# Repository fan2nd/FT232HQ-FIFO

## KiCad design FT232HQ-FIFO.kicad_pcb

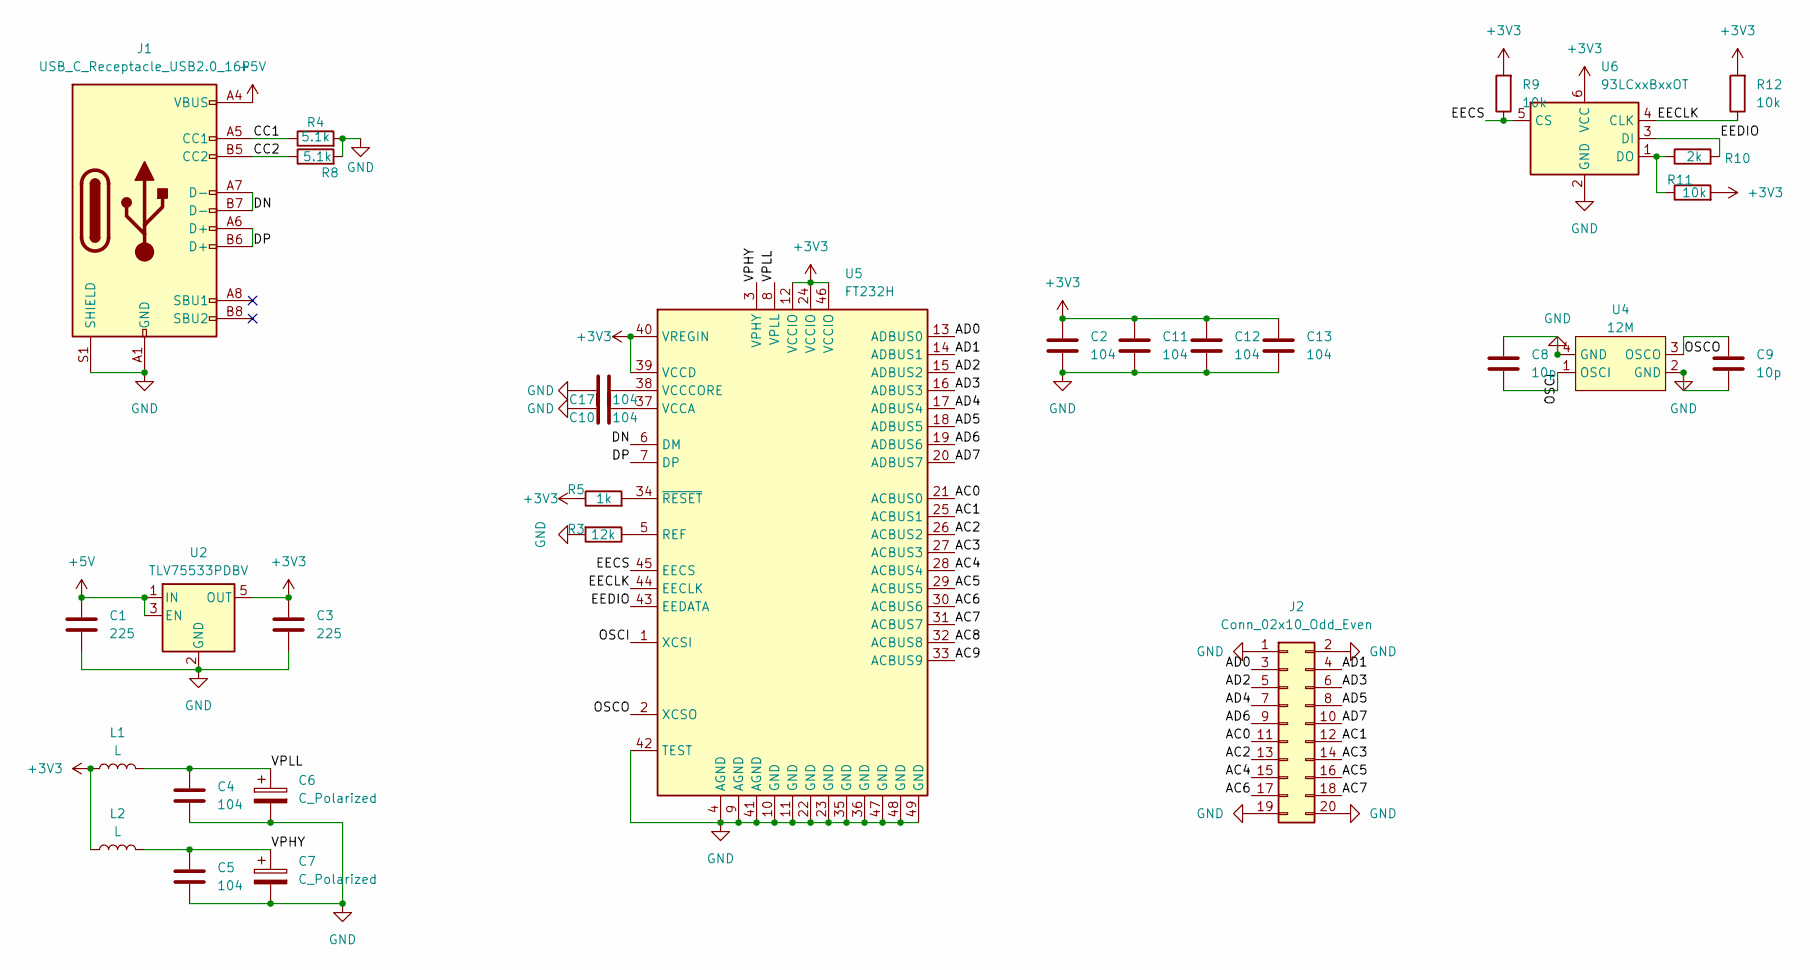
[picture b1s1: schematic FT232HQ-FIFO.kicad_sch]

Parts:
C1, C3: 225; C_0402_1005Metric
C2, C4, C5, C10, C11, C12, C13, C17: 104; C_0402_1005Metric
C6, C7: C_Polarized; C_0603_1608Metric
C8, C9: 10p; C_0402_1005Metric
J1: USB_C_Receptacle_USB2.0_16P; USB_C_Receptacle_TYPE-C-12P
J2: Conn_02x10_Odd_Even; PinHeader_2x10_P2.54mm_Vertical
L1, L2: L; L_0603_1608Metric
R3: 12k; R_0402_1005Metric
R4, R8: 5.1k; R_0402_1005Metric
R5: 1k; R_0402_1005Metric
R9, R11, R12: 10k; R_0402_1005Metric
R10: 2k; R_0402_1005Metric
U2: TLV75533PDBV; SOT-23-5
U4: 12M; Oscillator_SMD_13_3.2x2.5mm
U5: FT232H; QFN-48-1EP_8x8mm_P0.5mm_EP6.2x6.2mm
U6: 93LCxxBxxOT; SOT-23-6

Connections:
+3V3: C2.1, C3.1, C11.1, C12.1, C13.1, L1.1, L2.1, R5.1, R9.2, R11.2, R12.2, U2.5 (OUT), U5.12 (VCCIO), U5.24 (VCCIO), U5.39 (VCCD), U5.40 (VREGIN), U5.46 (VCCIO), U6.6 (VCC)
+5V: C1.1, J1.A4 (VBUS), J1.A9 (VBUS), J1.B4 (VBUS), J1.B9 (VBUS), U2.1 (IN), U2.3 (EN)
/AC0: J2.11, U5.21 (ACBUS0)
/AC1: J2.12, U5.25 (ACBUS1)
/AC2: J2.13, U5.26 (ACBUS2)
/AC3: J2.14, U5.27 (ACBUS3)
/AC4: J2.15, U5.28 (ACBUS4)
/AC5: J2.16, U5.29 (ACBUS5)
/AC6: J2.17, U5.30 (ACBUS6)
/AC7: J2.18, U5.31 (ACBUS7)
/AC8: U5.32 (ACBUS8)
/AC9: U5.33 (ACBUS9)
/AD0: J2.3, U5.13 (ADBUS0)
/AD1: J2.4, U5.14 (ADBUS1)
/AD2: J2.5, U5.15 (ADBUS2)
/AD3: J2.6, U5.16 (ADBUS3)
/AD4: J2.7, U5.17 (ADBUS4)
/AD5: J2.8, U5.18 (ADBUS5)
/AD6: J2.9, U5.19 (ADBUS6)
/AD7: J2.10, U5.20 (ADBUS7)
/CC1: J1.A5 (CC1), R4.1
/CC2: J1.B5 (CC2), R8.1
/DN: J1.A7 (D-), J1.B7 (D-), U5.6 (DM)
/DP: J1.A6 (D+), J1.B6 (D+), U5.7 (DP)
/EECLK: R12.1, U5.44 (EECLK), U6.4 (CLK)
/EECS: R9.1, U5.45 (EECS), U6.5 (CS)
/EEDIO: R10.2, U5.43 (EEDATA), U6.3 (DI)
/OSCI: C8.2, U4.1 (OSCI), U5.1 (XCSI)
/OSCO: C9.2, U4.3 (OSCO), U5.2 (XCSO)
/VPHY: C5.1, C7.1, L2.2, U5.3 (VPHY)
/VPLL: C4.1, C6.1, L1.2, U5.8 (VPLL)
GND: C1.2, C2.2, C3.2, C4.2, C5.2, C6.2, C7.2, C8.1, C9.1, C10.1, C11.2, C12.2, C13.2, C17.1, J1.A1 (GND), J1.A12 (GND), J1.B1 (GND), J1.B12 (GND), J1.S1 (SHIELD), J2.1, J2.2, J2.19, J2.20, R3.2, R4.2, R8.2, U2.2 (GND), U4.2 (GND), U4.4 (GND), U5.4 (AGND), U5.9 (AGND), U5.10 (GND), U5.11 (GND), U5.22 (GND), U5.23 (GND), U5.35 (GND), U5.36 (GND), U5.41 (AGND), U5.42 (TEST), U5.47 (GND), U5.48 (GND), U5.49 (GND), U6.2 (GND)
unnamed: R3.1, U5.5 (REF)
unnamed: C10.2, U5.37 (VCCA)
unnamed: C17.2, U5.38 (VCCCORE)
unnamed: R5.2, U5.34 (~RESET)
unnamed: R10.1, R11.1, U6.1 (DO)

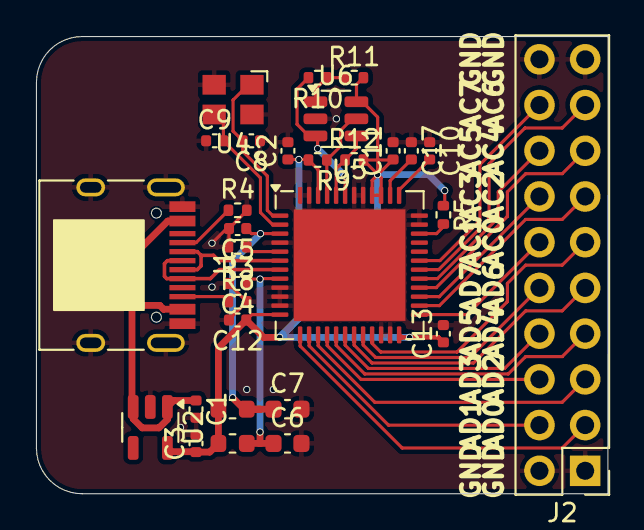
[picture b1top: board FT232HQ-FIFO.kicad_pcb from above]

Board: 2 copper layers, 31.8 x 25.4 mm, 30 parts (0 on the bottom side), 35 nets.
